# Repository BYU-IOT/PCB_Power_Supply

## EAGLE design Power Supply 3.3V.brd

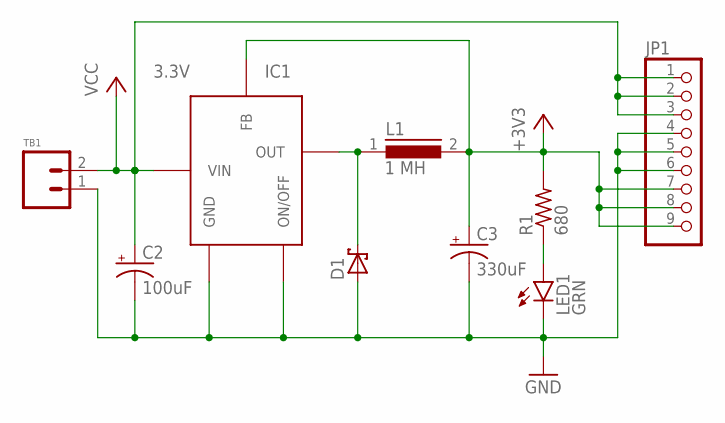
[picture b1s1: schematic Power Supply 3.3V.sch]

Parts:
C2: 100uF; F_CAP
C3: 330uF; F_CAP
D1: SCHOTTKY_DIODE; SMD_DIODE
IC1: 3.3V; TO-263-5
JP1: PINHD-1X9; 1X09
L1: 1 MH; DR125
LED1: GRN; 0603_LED
R1: 680; 0603_RESISTOR
TB1: TERMINAL_BLOCK_2

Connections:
+3V3: C3.+, IC1.4 (FB), JP1.7, JP1.8, JP1.9, L1.2, R1.2
GND: C2.-, C3.-, D1.A, IC1.3 (GND), IC1.5 (ON/OFF), JP1.4, JP1.5, JP1.6, LED1.C, TB1.1
unnamed: D1.C, IC1.2 (OUT), L1.1
unnamed: LED1.A, R1.1
VCC: C2.+, IC1.1 (VIN), JP1.1, JP1.2, JP1.3, TB1.2

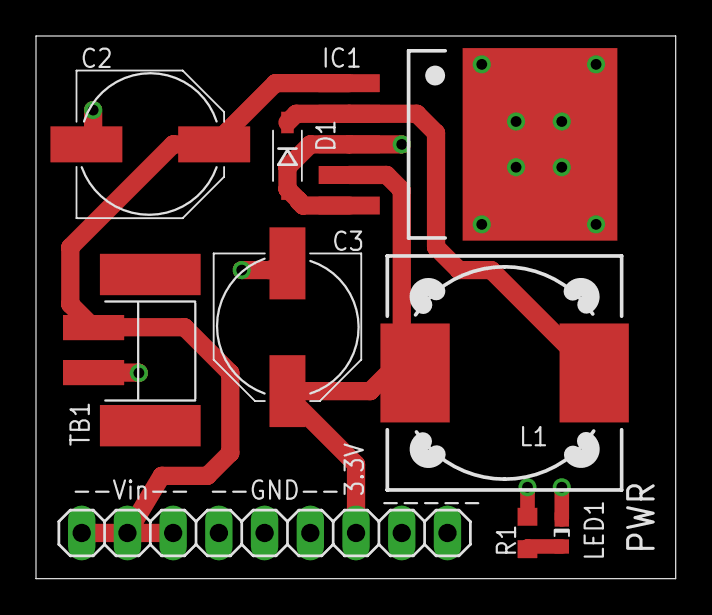
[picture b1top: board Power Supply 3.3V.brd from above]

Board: 4 copper layers, 35.5 x 30.1 mm, 9 parts (0 on the bottom side), 5 nets.

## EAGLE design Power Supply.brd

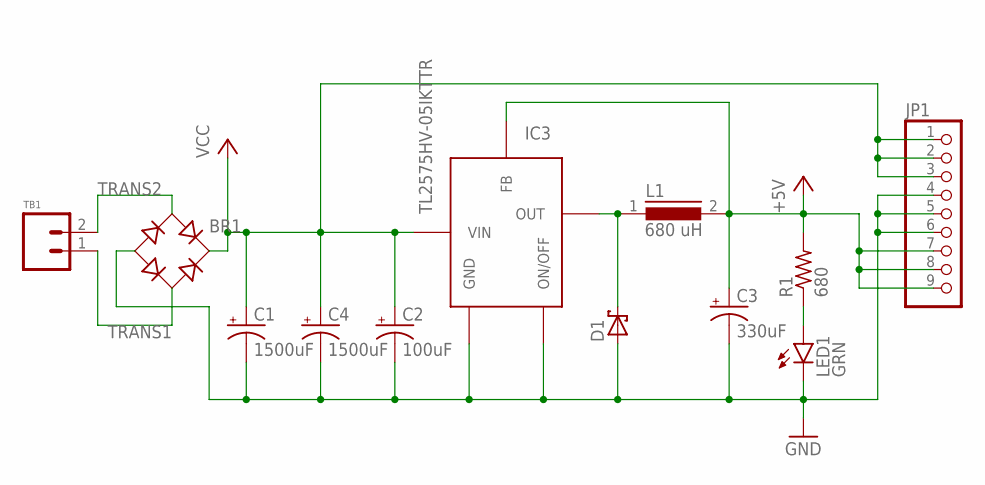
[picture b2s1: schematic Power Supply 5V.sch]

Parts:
BR1: BR; DFS
C1, C4: 1500uF; J16_CAP
C2: 100uF; F_CAP
C3: 330uF; F_CAP
D1: SCHOTTKY_DIODE; SMD_DIODE
IC3: TL2575HV-05IKTTR; TO-263-5
JP1: PINHD-1X9; 1X09
L1: 680 uH; DR125
LED1: GRN; 0603_LED
R1: 680; 0603_RESISTOR
TB1: TERMINAL_BLOCK_2

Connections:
+5V: C3.+, IC3.4 (FB), JP1.7, JP1.8, JP1.9, L1.2, R1.2
GND: BR1.-, C1.-, C2.-, C3.-, C4.-, D1.A, IC3.3 (GND), IC3.5 (ON/OFF), JP1.4, JP1.5, JP1.6, LED1.C
unnamed: D1.C, IC3.2 (OUT), L1.1
unnamed: LED1.A, R1.1
TRANS1: BR1.AC2, TB1.1
TRANS2: BR1.AC1, TB1.2
VCC: BR1.+, C1.+, C2.+, C4.+, IC3.1 (VIN), JP1.1, JP1.2, JP1.3

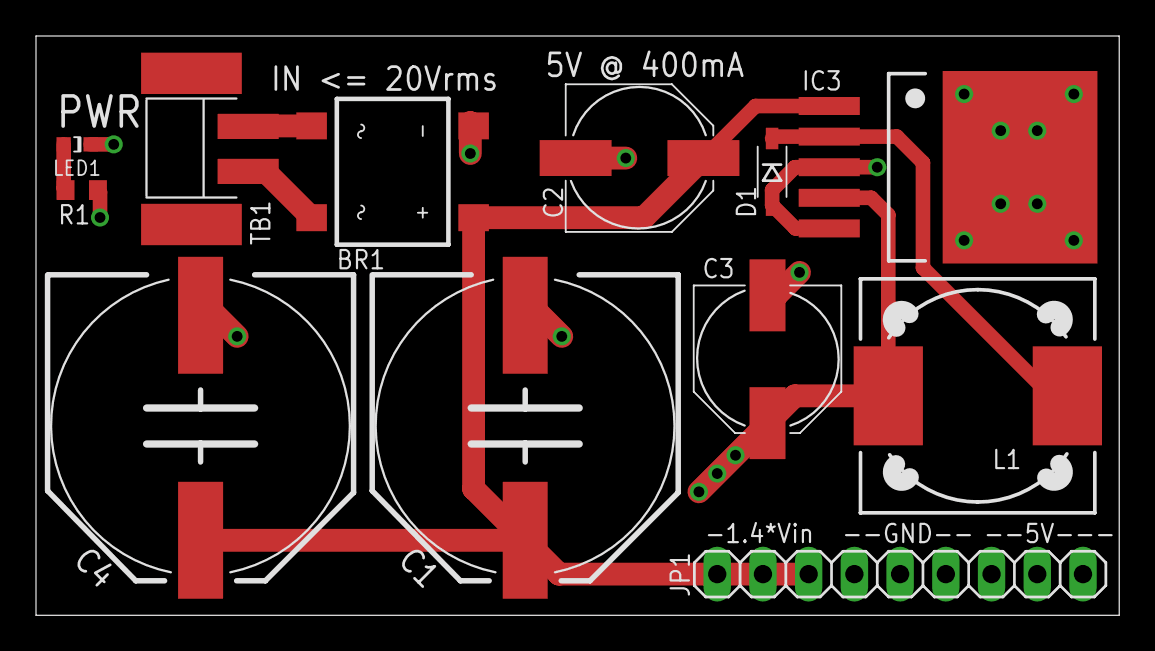
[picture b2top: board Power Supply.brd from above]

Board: 4 copper layers, 60.2 x 32.2 mm, 12 parts (0 on the bottom side), 7 nets.

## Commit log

2017-05-13 PCB design files for the 5 volt power supply
    This is the PCB design for the 5 volt power supply. It contains the
    gerber files and a bill of material (BOM) and a pdf of the schematic
    and finished files.
2018-09-27 Eagle Power Supply PCB
    It has both a 5V power supply and a 3.3V power supply
